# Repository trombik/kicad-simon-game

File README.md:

# Simon game

[Simon game with ATtiny13](https://hackaday.io/project/18952-simon-game-with-attiny13).

The code has been modified so that it can be compiled with GCC 11.2.0.

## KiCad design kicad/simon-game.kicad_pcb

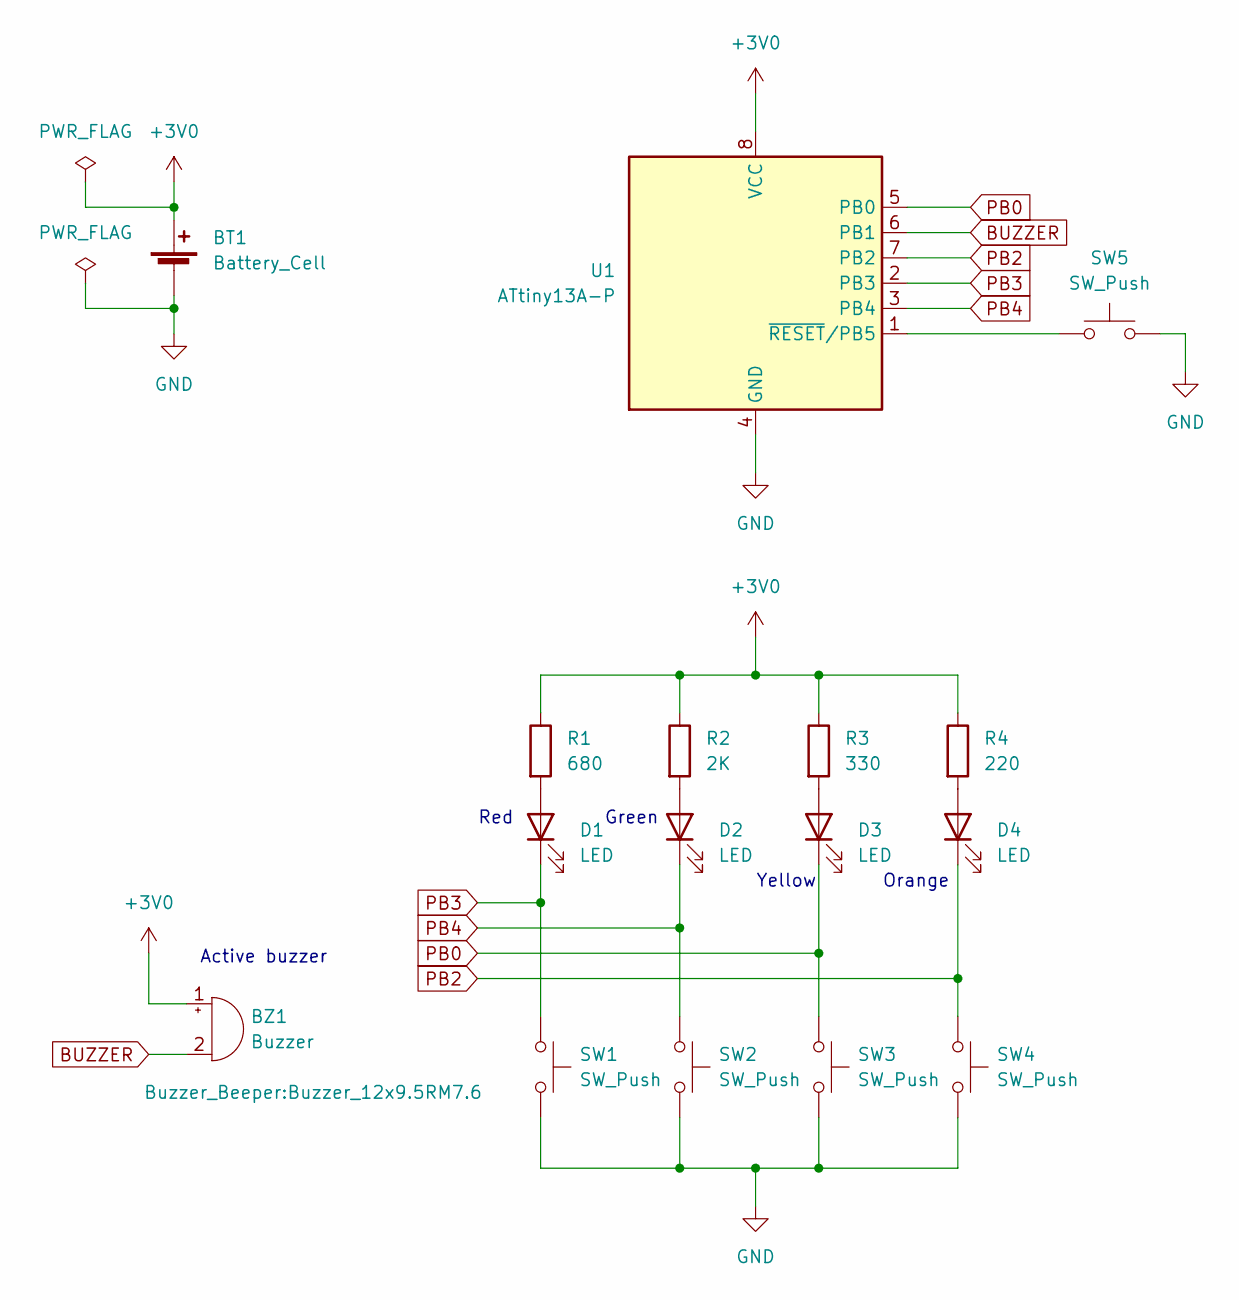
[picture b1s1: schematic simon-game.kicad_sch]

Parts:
BT1: Battery_Cell; BatteryHolder_Keystone_103_1x20mm
BZ1: Buzzer; Buzzer_12x9.5RM7.6
D1, D3: LED; LED_D3.0mm
D2, D4: LED; LED_D5.0mm
R1: 680; R_Axial_DIN0207_L6.3mm_D2.5mm_P7.62mm_Horizontal
R2: 2K; R_Axial_DIN0207_L6.3mm_D2.5mm_P7.62mm_Horizontal
R3: 330; R_Axial_DIN0309_L9.0mm_D3.2mm_P12.70mm_Horizontal
R4: 220; R_Axial_DIN0207_L6.3mm_D2.5mm_P10.16mm_Horizontal
SW1, SW2, SW3, SW4: SW_Push; SW_PUSH-12mm
SW5: SW_Push; SW_PUSH_6mm
U1: ATtiny13A-P; DIP-8_W7.62mm

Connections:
+3V0: BT1.1 (+), BZ1.1 (-), R1.1, R2.1, R3.1, R4.1, U1.8 (VCC)
BUZZER: BZ1.2 (+), U1.6 (PB1)
GND: BT1.2 (-), SW1.2, SW2.2, SW3.2, SW4.2, SW5.2, U1.4 (GND)
unnamed: D1.2 (A), R1.2
unnamed: D2.2 (A), R2.2
unnamed: D3.2 (A), R3.2
unnamed: D4.2 (A), R4.2
unnamed: SW5.1, U1.1 (~RESET/PB5)
PB0: D3.1 (K), SW3.1, U1.5 (PB0)
PB2: D4.1 (K), SW4.1, U1.7 (PB2)
PB3: D1.1 (K), SW1.1, U1.2 (PB3)
PB4: D2.1 (K), SW2.1, U1.3 (PB4)

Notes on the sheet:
Red
Orange
Yellow
Green
Active buzzer

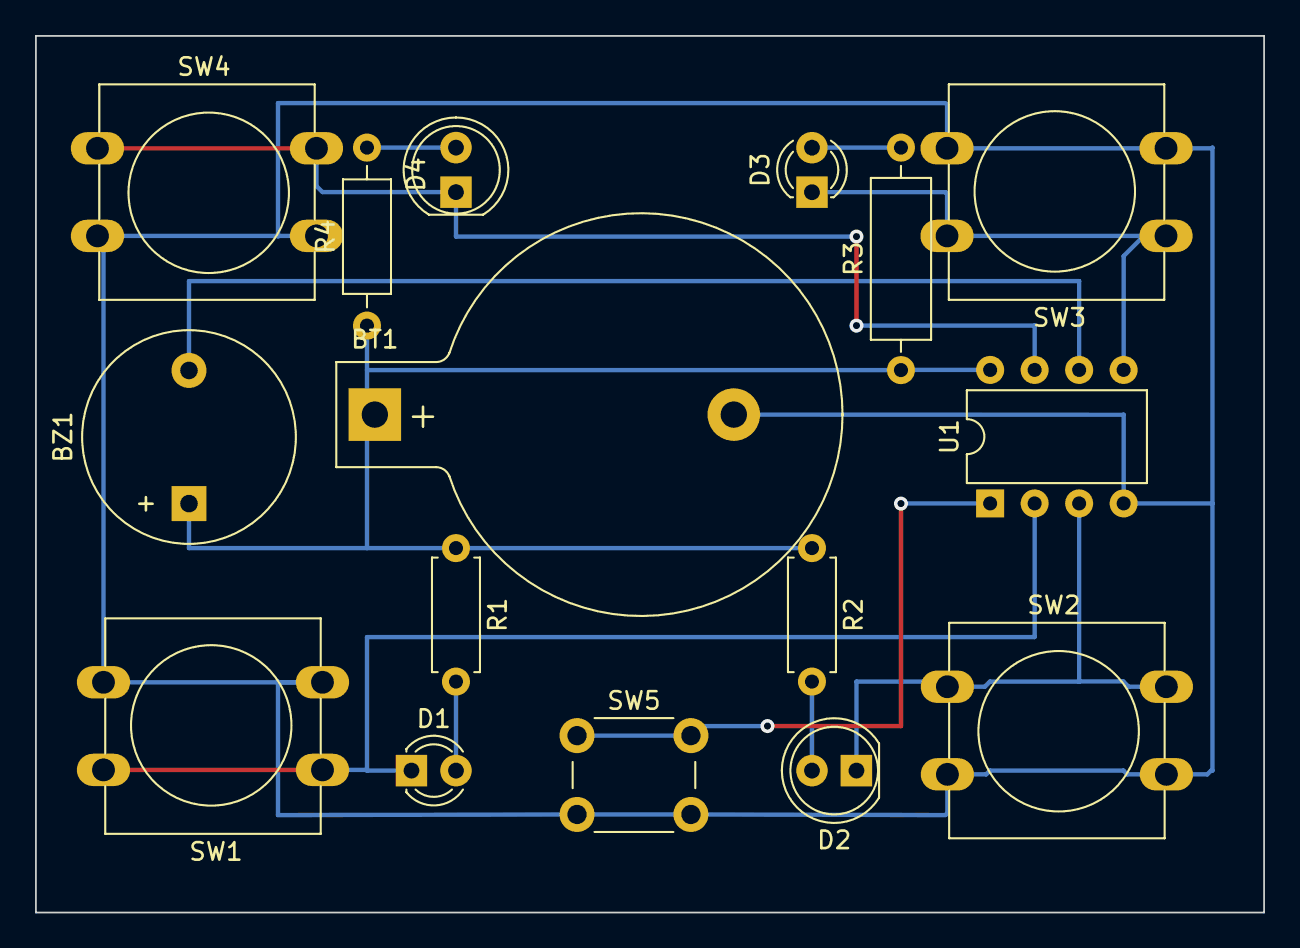
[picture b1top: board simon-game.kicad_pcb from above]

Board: 2 copper layers, 70.1 x 50.0 mm, 16 parts (0 on the bottom side), 12 nets.

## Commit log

2022-08-29 initial import
2022-08-29 bugfix: optimize the size
    with recent GCC, the size overflows.
    also:
    * change a tone freq for my own speaker
    * do not build infinite loop function by default
    * add SIMON_RANDOM_LFSR, which reduces size a bit
2022-08-29 feat: add pio and tox for build
2022-08-29 feat: add schematic
2022-08-29 update: .gitignore
2022-08-29 doc: add README and LICENSE
